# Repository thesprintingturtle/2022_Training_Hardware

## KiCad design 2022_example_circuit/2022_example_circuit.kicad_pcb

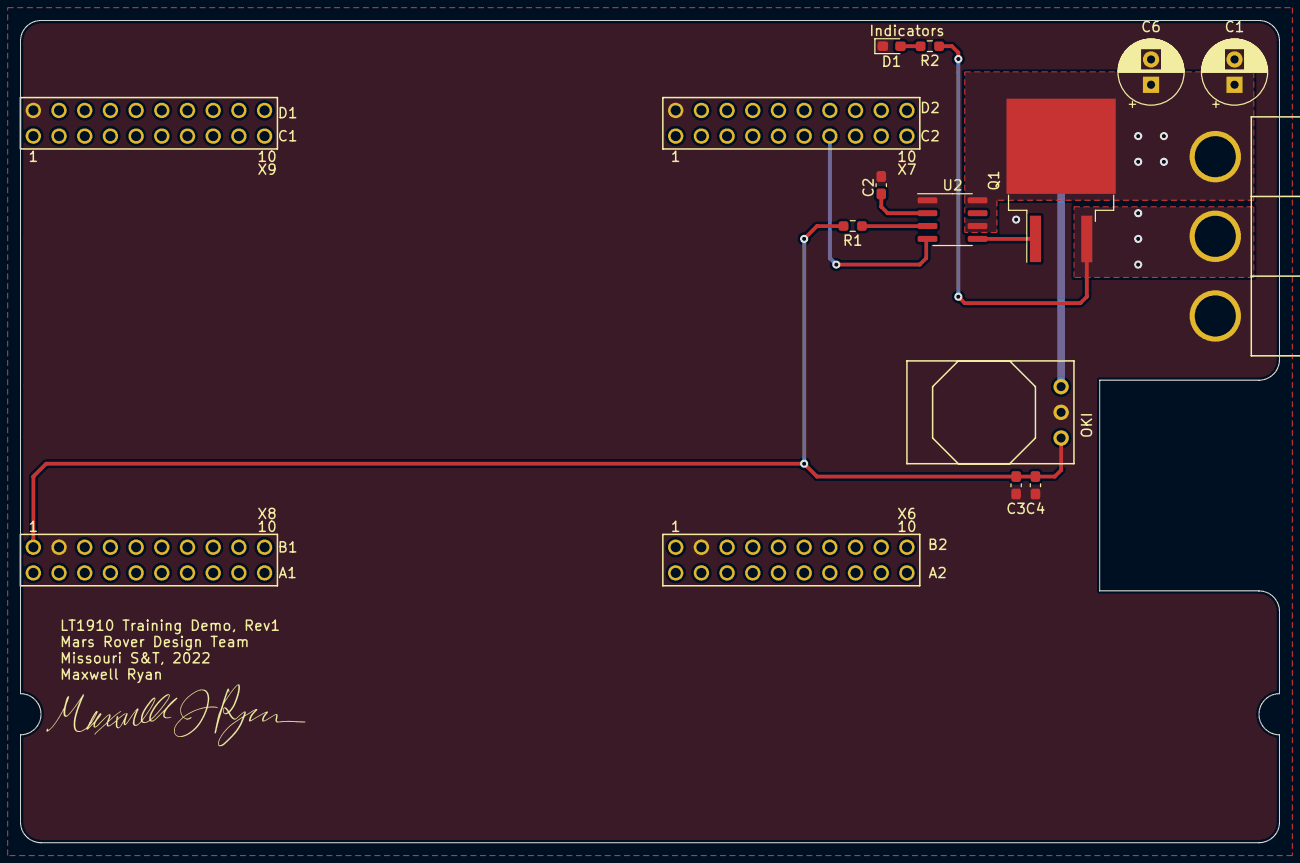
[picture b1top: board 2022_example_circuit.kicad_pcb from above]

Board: 2 copper layers, 124.5 x 81.3 mm, 13 parts (0 on the bottom side), 9 nets.

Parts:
C1: 22uF 50V; CP_Radial_D6.3mm_P2.50mm
C2: 0.1uF; C_0603_1608Metric_Pad1.08x0.95mm_HandSolder
C3: 10u; C_0603_1608Metric_Pad1.08x0.95mm_HandSolder
C4: 0.1u; C_0603_1608Metric_Pad1.08x0.95mm_HandSolder
C6: 10uF 50V; CP_Radial_D6.3mm_P2.50mm
Conn1: AndersonPP; Anderson_3_Horizontal_Side_by_Side
D1: LED; LED_0603_1608Metric_Pad1.05x0.95mm_HandSolder
Q1: IRFS4115; TO-263-2
R1: 5.1k; R_0603_1608Metric_Pad0.98x0.95mm_HandSolder
R2: 3300; R_0603_1608Metric_Pad0.98x0.95mm_HandSolder
U1: OKI; OKI_Horizontal
U2: LT1910; SOIC-8_3.9x4.9mm_P1.27mm
U3: TM4C129E_Launchpad; TM4C129E_Launchpad_FULL_THT_TOP

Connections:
+5V: C3.1, C4.1, R1.2, U1.3, U3.+5V
A1_signal: U2.4, U3.PH0
Anderson1: Conn1.2, Q1.3, R2.1
GND: C1.2, C2.2, C3.2, C4.2, C6.2, Conn1.1, D1.1, U1.2, U2.1, U3.GND
unnamed: C2.1, U2.2
unnamed: D1.2, R2.2
unnamed: Q1.1, U2.5
unnamed: R1.1, U2.3
PV: C1.1, C6.1, Conn1.3, Q1.2, U1.1, U2.6, U2.8

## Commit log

2021-09-18 inital commit
2021-09-18 Made LT1910_Example_Circuit
